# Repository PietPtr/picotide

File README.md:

# PicoTide

Repository filled with experimental crates and libraries for a [bittide](https://www.bittide.io/) style

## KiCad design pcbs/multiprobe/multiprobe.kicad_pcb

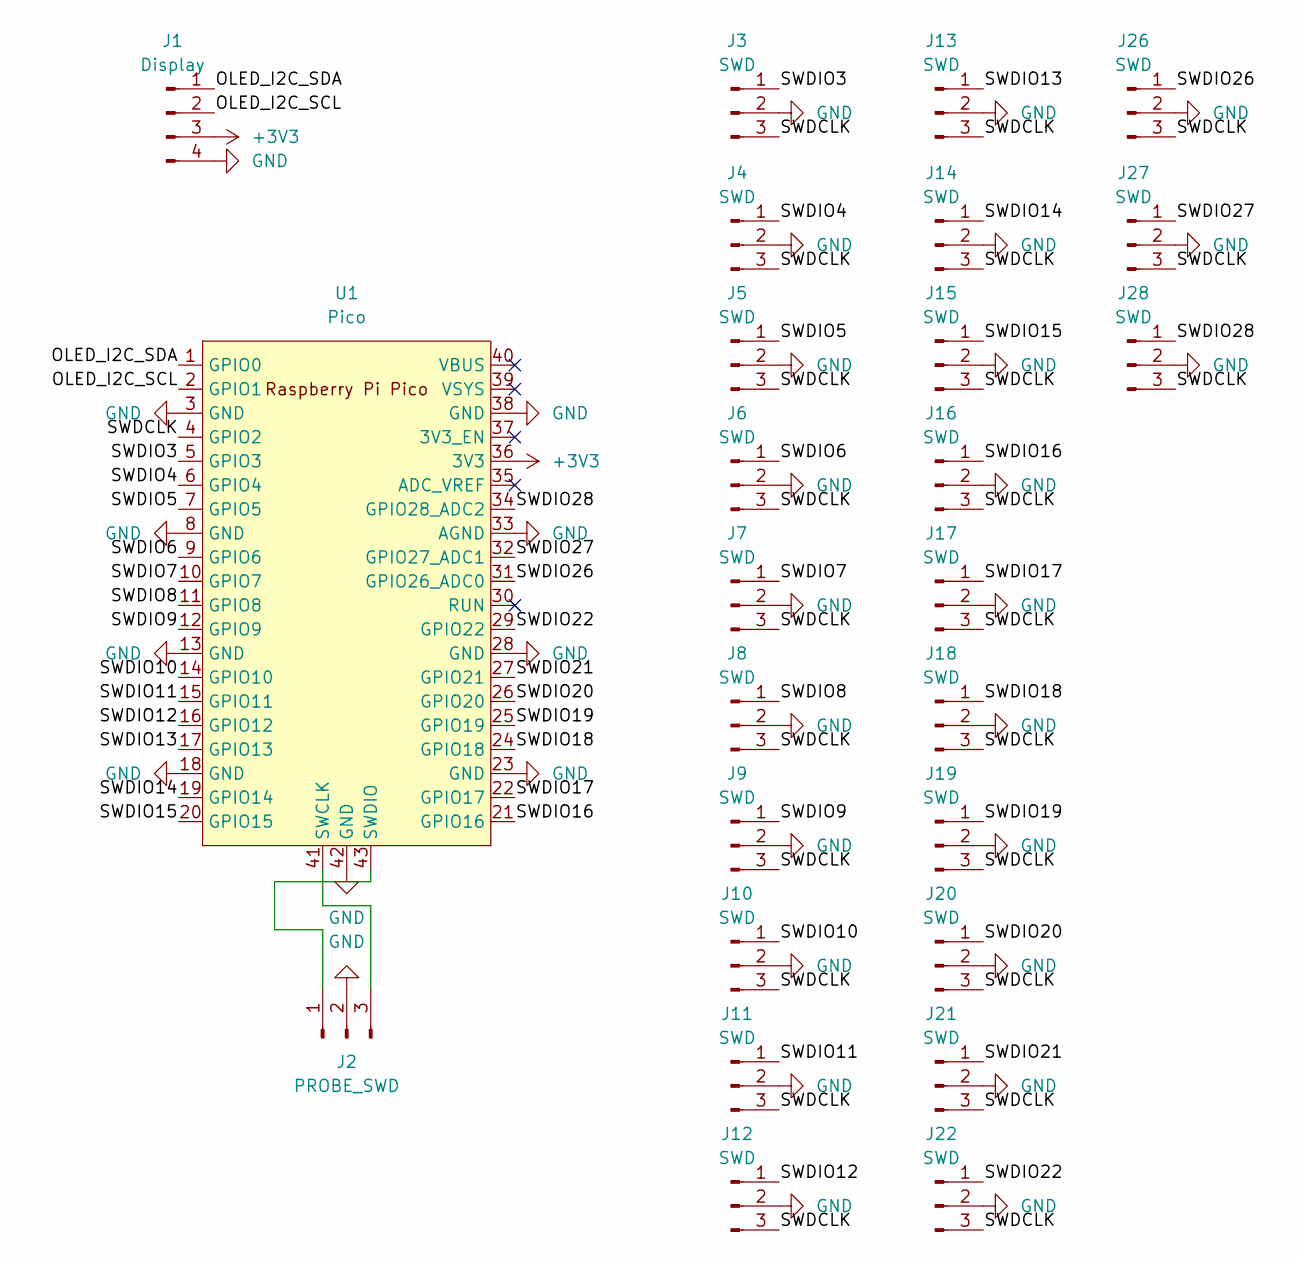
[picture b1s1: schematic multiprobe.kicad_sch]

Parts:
J1: Display; PinHeader_1x04_P2.54mm_Vertical
J2: PROBE_SWD; SWD
J3, J4, J5, J6, J7, J8, J9, J10, J11, J12, J13, J14, J15, J16, J17, J18, J19, J20, J21, J22, J26, J27, J28: SWD
U1: Pico; RPi_Pico_SMD_TH

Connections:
+3V3: J1.3, U1.36 (3V3)
/OLED_I2C_SCL: J1.2, U1.2 (GPIO1)
/OLED_I2C_SDA: J1.1, U1.1 (GPIO0)
/SWDCLK: J3.3, J4.3, J5.3, J6.3, J7.3, J8.3, J9.3, J10.3, J11.3, J12.3, J13.3, J14.3, J15.3, J16.3, J17.3, J18.3, J19.3, J20.3, J21.3, J22.3, J26.3, J27.3, J28.3, U1.4 (GPIO2)
/SWDIO3: J3.1, U1.5 (GPIO3)
/SWDIO4: J4.1, U1.6 (GPIO4)
/SWDIO5: J5.1, U1.7 (GPIO5)
/SWDIO6: J6.1, U1.9 (GPIO6)
/SWDIO7: J7.1, U1.10 (GPIO7)
/SWDIO8: J8.1, U1.11 (GPIO8)
/SWDIO9: J9.1, U1.12 (GPIO9)
/SWDIO10: J10.1, U1.14 (GPIO10)
/SWDIO11: J11.1, U1.15 (GPIO11)
/SWDIO12: J12.1, U1.16 (GPIO12)
/SWDIO13: J13.1, U1.17 (GPIO13)
/SWDIO14: J14.1, U1.19 (GPIO14)
/SWDIO15: J15.1, U1.20 (GPIO15)
/SWDIO16: J16.1, U1.21 (GPIO16)
/SWDIO17: J17.1, U1.22 (GPIO17)
/SWDIO18: J18.1, U1.24 (GPIO18)
/SWDIO19: J19.1, U1.25 (GPIO19)
/SWDIO20: J20.1, U1.26 (GPIO20)
/SWDIO21: J21.1, U1.27 (GPIO21)
/SWDIO22: J22.1, U1.29 (GPIO22)
/SWDIO26: J26.1, U1.31 (GPIO26_ADC0)
/SWDIO27: J27.1, U1.32 (GPIO27_ADC1)
/SWDIO28: J28.1, U1.34 (GPIO28_ADC2)
GND: J1.4, J2.2, J3.2, J4.2, J5.2, J6.2, J7.2, J8.2, J9.2, J10.2, J11.2, J12.2, J13.2, J14.2, J15.2, J16.2, J17.2, J18.2, J19.2, J20.2, J21.2, J22.2, J26.2, J27.2, J28.2, U1.3 (GND), U1.8 (GND), U1.13 (GND), U1.18 (GND), U1.23 (GND), U1.28 (GND), U1.33 (AGND), U1.38 (GND), U1.42 (GND)
unnamed: J2.1, U1.43 (SWDIO)
unnamed: J2.3, U1.41 (SWCLK)

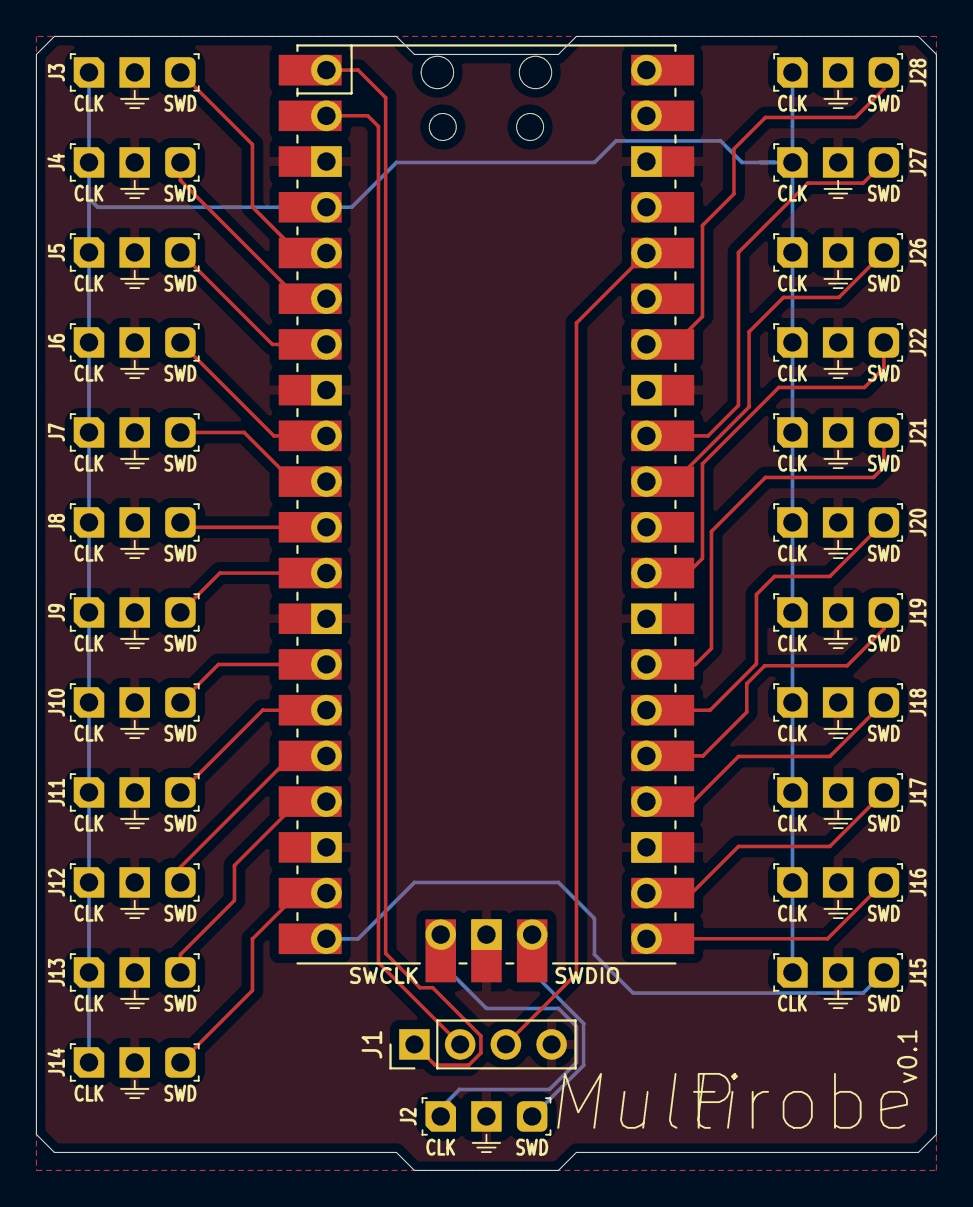
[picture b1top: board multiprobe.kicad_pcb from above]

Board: 2 copper layers, 50.0 x 63.0 mm, 26 parts (0 on the bottom side), 30 nets.

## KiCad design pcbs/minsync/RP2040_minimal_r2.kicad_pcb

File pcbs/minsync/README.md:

# `minsync`

A minimal testbed for a RP2040-based board with an Si5351 as a clock source instead of the usual 12MHz crystal. 

# IO:

- Four clusters of six GPIO pins and 5V + GND power pins to allow easy chaining of the board.
- Headers for SWD flashing
- A bootsel button
- Testpoint for a gpout pin for debugging internal clocks

# Components

Si5351A (0.77): https://jlcpcb.com/partdetail/skyworks_siliconLabs-SI5351A_BGTR/C504891 
25 MHz crystal (0.25): https://jlcpcb.com/partdetail/Ndk-NX3225GA_25_000M_STD_CRG2/C1985619
RP2040 (0.95): https://jlcpcb.com/partdetail/RaspberryPi-RP2040/C2040
Voltage regulator (0.51): https://jlcpcb.com/partdetail/Onsemi-NCP1117DT33G/C154606
quad SPI flash (0.51): https://jlcpcb.com/partdetail/WinbondElec-W25Q128JVSIQ/C97521
Button for reset (0.57): https://jlcpcb.com/partdetail/ck-KMR221GLFS/C72443
Male headers x4 (0.60): https://jlcpcb.com/partdetail/225573-A2005WV2x5P/C225290

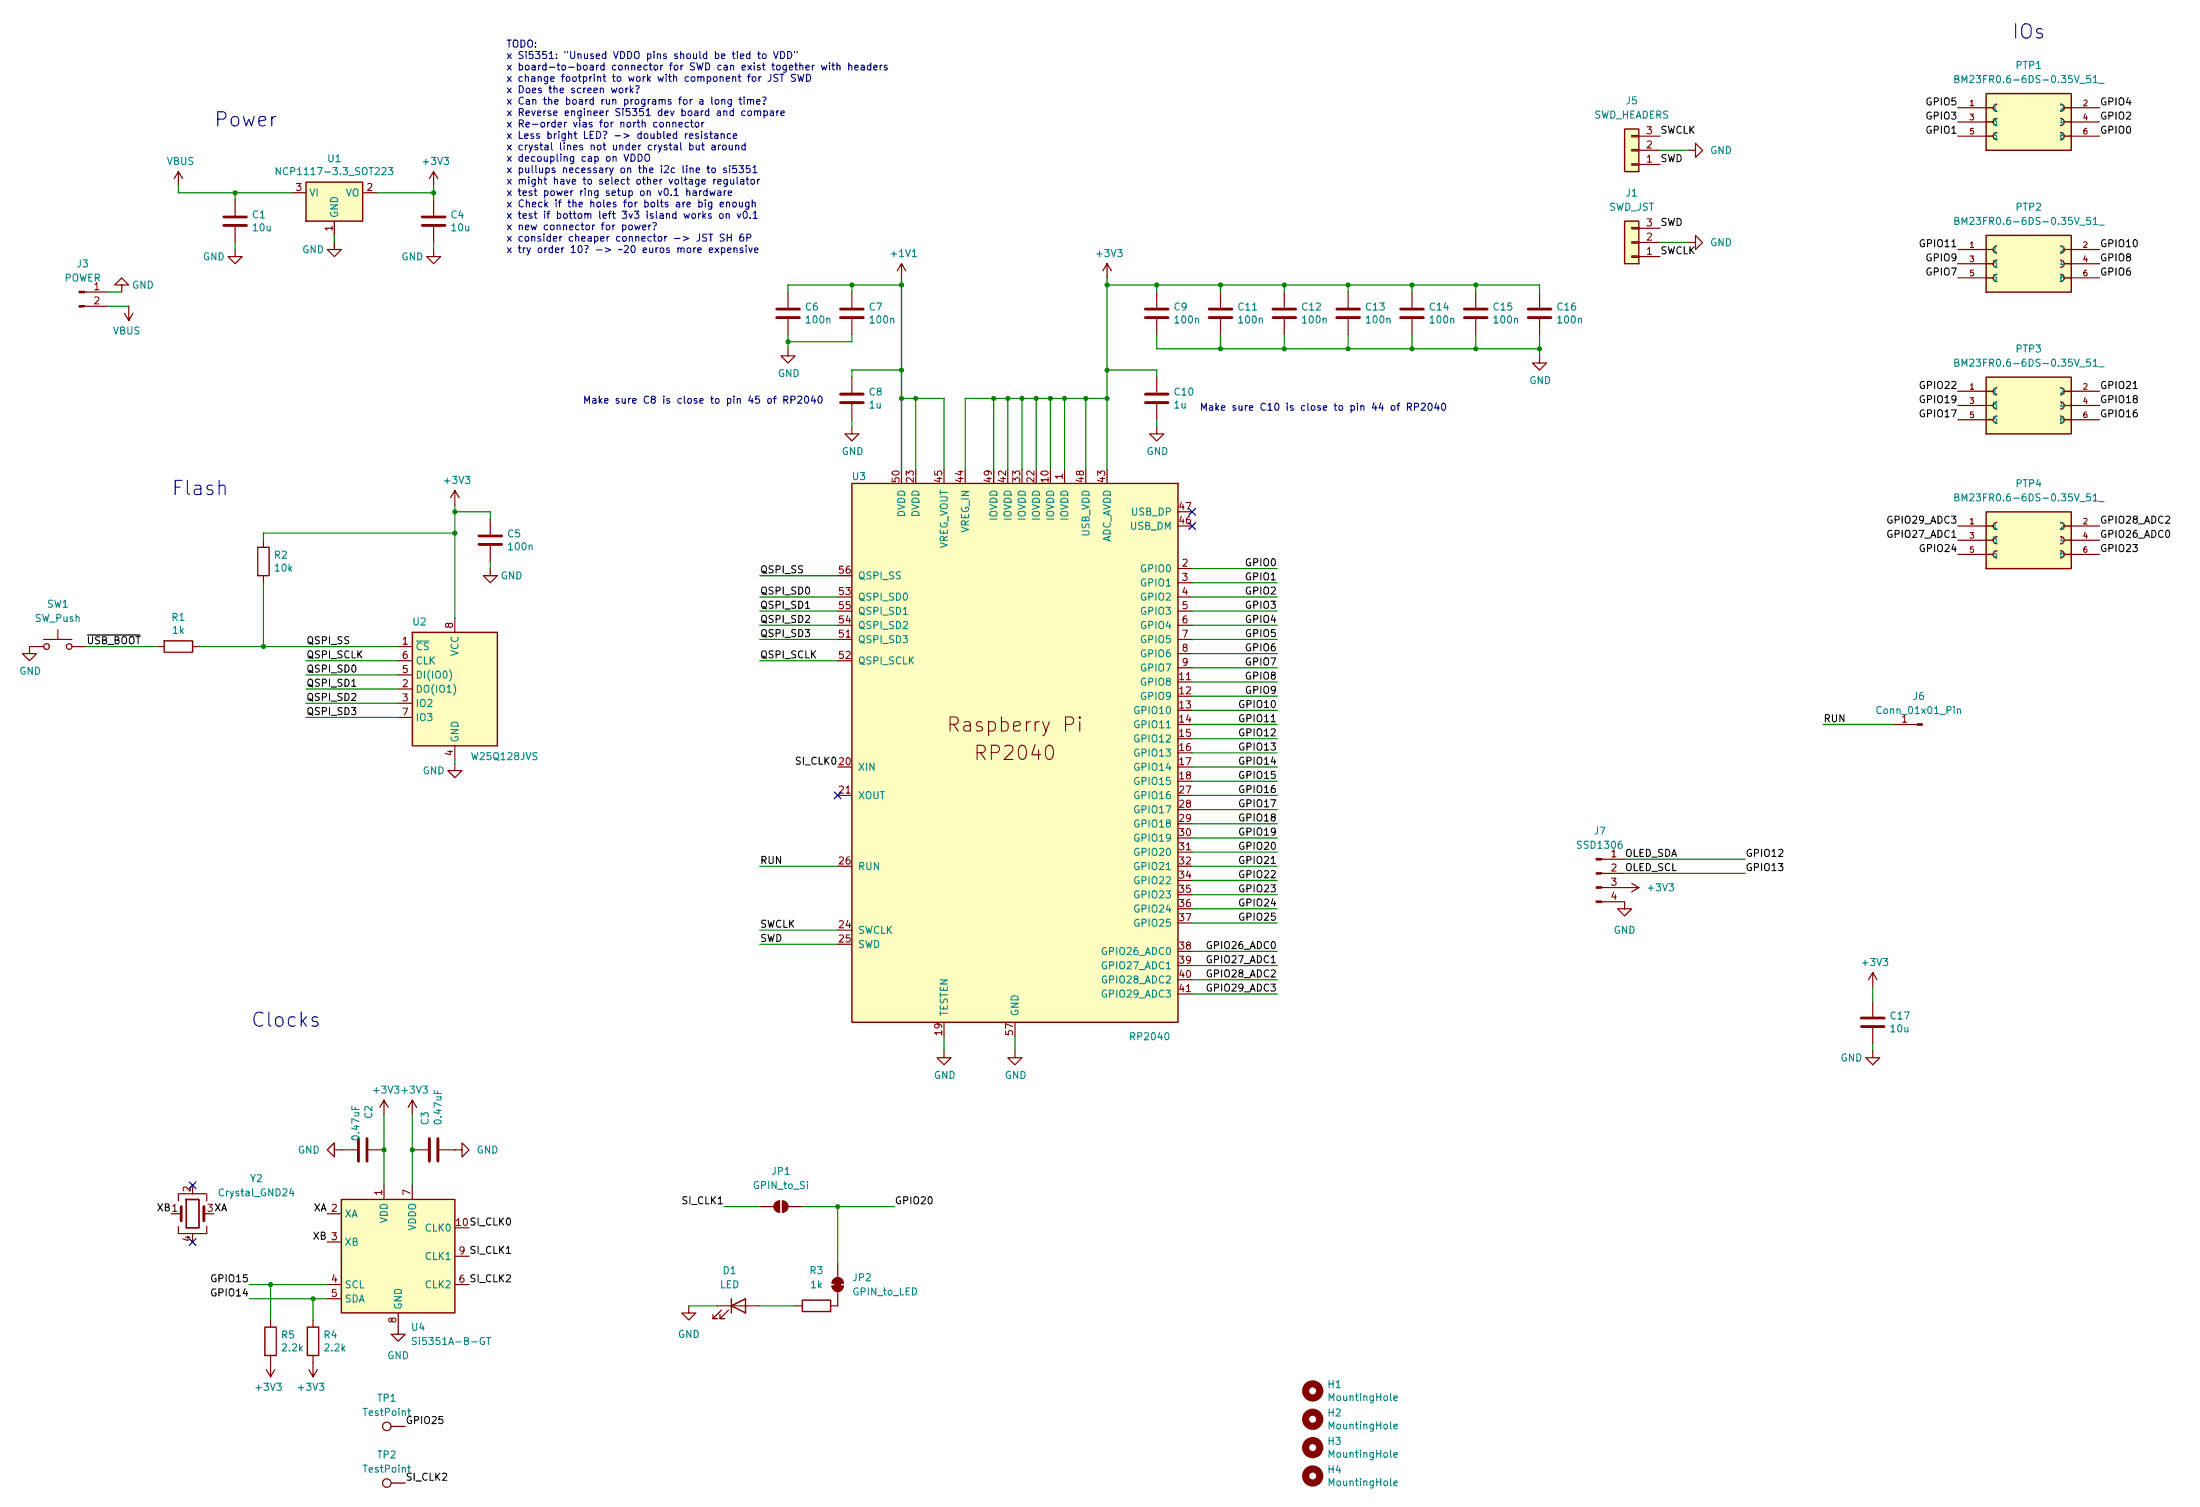
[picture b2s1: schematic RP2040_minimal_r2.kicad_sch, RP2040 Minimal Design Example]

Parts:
C1, C4, C17: 10u; C_0805_2012Metric
C2, C3: 0.47uF; C_0603_1608Metric
C5, C6, C7, C9, C11, C12, C13, C14, C15, C16: 100n; C_0402_1005Metric
C8, C10: 1u; C_0402_1005Metric
D1: LED; LED_0603_1608Metric
H1, H2, H3, H4: MountingHole; MountingHole_2.7mm_M2.5
J1: SWD_JST; JST_SH_BM03B-SRSS-TB_1x03-1MP_P1.00mm_Vertical; LCSC C160389
J3: POWER; PinHeader_1x02_P2.54mm_Vertical
J5: SWD_HEADERS; PinHeader_1x03_P2.54mm_Vertical
J6: Conn_01x01_Pin; PinHeader_1x01_P1.27mm_Vertical
J7: SSD1306; PinHeader_1x04_P2.54mm_Vertical
JP1: GPIN_to_Si; SolderJumper-2_P1.3mm_Open_RoundedPad1.0x1.5mm
JP2: GPIN_to_LED; SolderJumper-2_P1.3mm_Bridged_RoundedPad1.0x1.5mm
PTP1, PTP2, PTP3, PTP4: BM23FR0.6-6DS-0.35V_51_; JST_SH_BM06B-SRSS-TB_1x06-1MP_P1.00mm_Vertical; PARTREV 16.11.07; DigiKey_Part_Number 26-BM23FR0.6-6DS-0.35V(51)TR-ND
R1, R3: 1k; R_0402_1005Metric
R2: 10k; R_0402_1005Metric
R4, R5: 2.2k; R_0402_1005Metric
SW1: SW_Push; TS-1187A-PushButton; LCSC C72443
TP1, TP2: TestPoint; PinHeader_1x01_P2.54mm_Vertical
U1: NCP1117-3.3_SOT223; SOT-223-3_TabPin2; LCSC C154606
U2: W25Q128JVS; SOIC-8_5.23x5.23mm_P1.27mm; LCSC C97521
U3: RP2040; RP2040-QFN-56; LCSC C2040
U4: Si5351A-B-GT; MSOP-10_3x3mm_P0.5mm; LCSC C504891
Y2: Crystal_GND24; Crystal_SMD_3225-4Pin_3.2x2.5mm; LCSC C1985619

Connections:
+1V1: C6.1, C7.1, C8.1, U3.23 (DVDD), U3.45 (VREG_VOUT), U3.50 (DVDD)
+3V3: C2.1, C3.1, C4.1, C5.1, C9.1, C10.1, C11.1, C12.1, C13.1, C14.1, C15.1, C16.1, C17.1, J7.3, R2.1, R4.2, R5.2, U1.2 (VO), U2.8 (VCC), U3.1 (IOVDD), U3.10 (IOVDD), U3.22 (IOVDD), U3.33 (IOVDD), U3.42 (IOVDD), U3.43 (ADC_AVDD), U3.44 (VREG_IN), U3.48 (USB_VDD), U3.49 (IOVDD), U4.1 (VDD), U4.7 (VDDO)
/GPIO0: PTP1.6, U3.2 (GPIO0)
/GPIO1: PTP1.5, U3.3 (GPIO1)
/GPIO2: PTP1.4, U3.4 (GPIO2)
/GPIO3: PTP1.3, U3.5 (GPIO3)
/GPIO4: PTP1.2, U3.6 (GPIO4)
/GPIO5: PTP1.1, U3.7 (GPIO5)
/GPIO6: PTP2.6, U3.8 (GPIO6)
/GPIO7: PTP2.5, U3.9 (GPIO7)
/GPIO8: PTP2.4, U3.11 (GPIO8)
/GPIO9: PTP2.3, U3.12 (GPIO9)
/GPIO10: PTP2.2, U3.13 (GPIO10)
/GPIO11: PTP2.1, U3.14 (GPIO11)
/GPIO12: J7.1, U3.15 (GPIO12)
/GPIO13: J7.2, U3.16 (GPIO13)
/GPIO14: R4.1, U3.17 (GPIO14), U4.5 (SDA)
/GPIO15: R5.1, U3.18 (GPIO15), U4.4 (SCL)
/GPIO16: PTP3.6, U3.27 (GPIO16)
/GPIO17: PTP3.5, U3.28 (GPIO17)
/GPIO18: PTP3.4, U3.29 (GPIO18)
/GPIO19: PTP3.3, U3.30 (GPIO19)
/GPIO20: JP1.2 (B), JP2.2 (B), U3.31 (GPIO20)
/GPIO21: PTP3.2, U3.32 (GPIO21)
/GPIO22: PTP3.1, U3.34 (GPIO22)
/GPIO23: PTP4.6, U3.35 (GPIO23)
/GPIO24: PTP4.5, U3.36 (GPIO24)
/GPIO25: TP1.1, U3.37 (GPIO25)
/GPIO26_ADC0: PTP4.4, U3.38 (GPIO26_ADC0)
/GPIO27_ADC1: PTP4.3, U3.39 (GPIO27_ADC1)
/GPIO28_ADC2: PTP4.2, U3.40 (GPIO28_ADC2)
/GPIO29_ADC3: PTP4.1, U3.41 (GPIO29_ADC3)
/QSPI_SCLK: U2.6 (CLK), U3.52 (QSPI_SCLK)
/QSPI_SD0: U2.5 (DI(IO0)), U3.53 (QSPI_SD0)
/QSPI_SD1: U2.2 (DO(IO1)), U3.55 (QSPI_SD1)
/QSPI_SD2: U2.3 (IO2), U3.54 (QSPI_SD2)
/QSPI_SD3: U2.7 (IO3), U3.51 (QSPI_SD3)
/QSPI_SS: R1.1, R2.2, U2.1 (~CS), U3.56 (QSPI_SS)
/RUN: J6.1, U3.26 (RUN)
/SI_CLK0: U3.20 (XIN), U4.10 (CLK0)
/SI_CLK1: JP1.1 (A), U4.9 (CLK1)
/SI_CLK2: TP2.1, U4.6 (CLK2)
/SWCLK: J1.1, J5.3, U3.24 (SWCLK)
/SWD: J1.3, J5.1, U3.25 (SWD)
/XA: U4.2 (XA), Y2.3
/XB: U4.3 (XB), Y2.1
/~USB_BOOT: R1.2, SW1.2
GND: C1.2, C2.2, C3.2, C4.2, C5.2, C6.2, C7.2, C8.2, C9.2, C10.2, C11.2, C12.2, C13.2, C14.2, C15.2, C16.2, C17.2, D1.1 (K), J1.2, J3.1, J5.2, J7.4, SW1.1, U1.1 (GND), U2.4 (GND), U3.19 (TESTEN), U3.57 (GND), U4.8 (GND)
unnamed: D1.2 (A), R3.1
unnamed: JP2.1 (A), R3.2
VBUS: C1.1, J3.2, U1.3 (VI)

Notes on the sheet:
IOs
Power
Clocks
Make sure C8 is close to pin 45 of RP2040
Make sure C10 is close to pin 44 of RP2040
Flash
TODO: x Si5351: "Unused VDDO pins should be tied to VDD" x board-to-board connector for SWD can exist together with headers x change footprint to work with component for JST SWD x Does the screen work? x Can the board run programs for a long time? x Reverse engineer Si5351 dev board and compare x R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

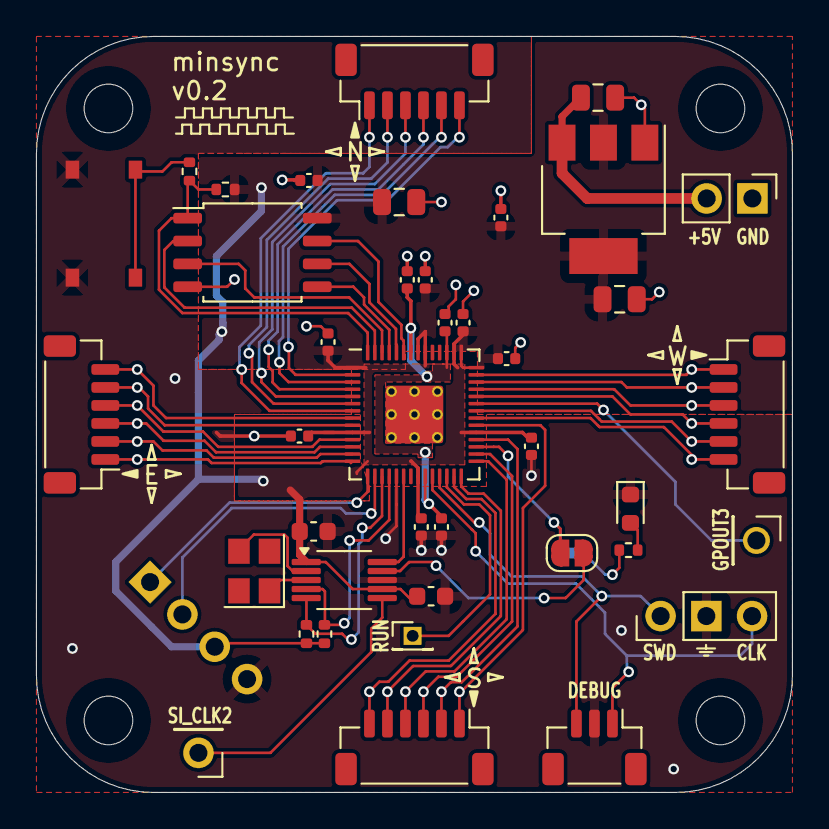
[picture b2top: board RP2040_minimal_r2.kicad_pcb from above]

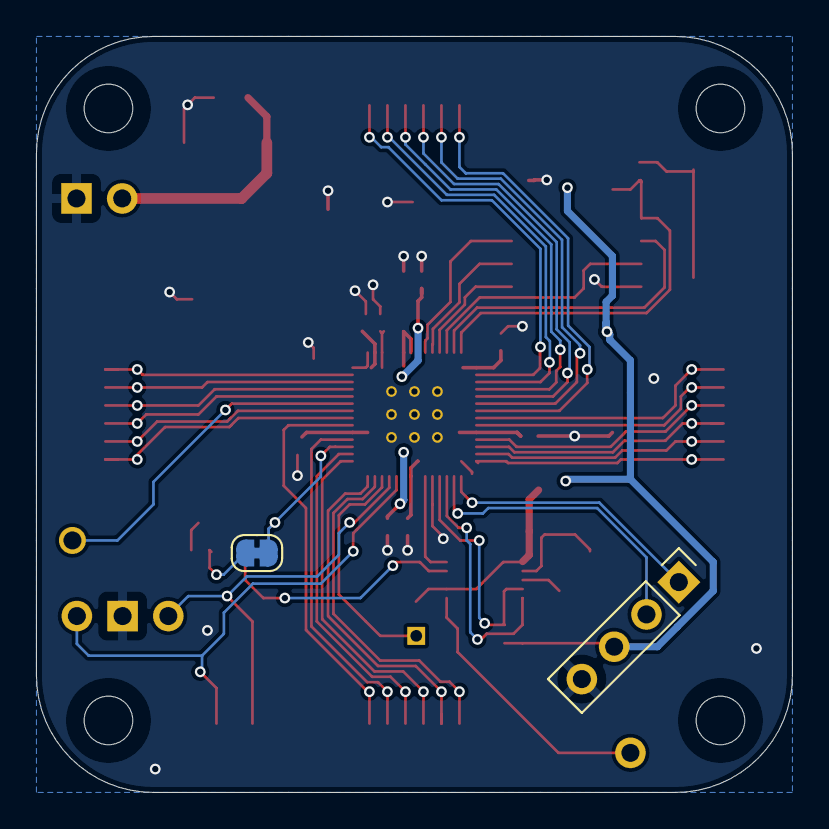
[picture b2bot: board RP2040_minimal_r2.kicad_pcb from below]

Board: 2 copper layers, 42.0 x 42.0 mm, 46 parts (2 on the bottom side), 51 nets.

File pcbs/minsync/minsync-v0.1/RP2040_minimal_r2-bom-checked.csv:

Comment,Designator,Footprint,LCSC
10u,"C1,C4,C17",Capacitor_SMD:C_0805_2012Metric,C15850
100n,"C2,C5,C6,C7,C9,C11,C12,C13,C14,C15,C16",Capacitor_SMD:C_0402_1005Metric,C1525
1u,"C8,C10",Capacitor_SMD:C_0402_1005Metric,C52923
LED,D1,LED_SMD:LED_0603_1608Metric,C2290
1k,R1,Resistor_SMD:R_0402_1005Metric,C11702
10k,R2,Resistor_SMD:R_0402_1005Metric,C25744
470R,R3,Resistor_SMD:R_0402_1005Metric,C25117
SW_Push,SW1,Button_Switch_SMD:SW_Push_SPST_NO_Alps_SKRK,C318884
NCP1117-3.3_SOT223,U1,Package_TO_SOT_SMD:SOT-223-3_TabPin2,C146799
W25Q128JVS,U2,Package_SO:SOIC-8_5.23x5.23mm_P1.27mm,C97521
RP2040,U3,RP2040_minimal:RP2040-QFN-56,C2040
Si5351A-B-GT,U4,Package_SO:MSOP-10_3x3mm_P0.5mm,C504891
Crystal_GND24,Y2,Crystal:Crystal_SMD_3225-4Pin_3.2x2.5mm,C1985619

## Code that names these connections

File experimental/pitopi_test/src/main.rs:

#![no_std]
#![no_main]

#[link_section = ".boot2"]
#[no_mangle]
#[used]
pub static BOOT2_FIRMWARE: [u8; 256] = rp2040_boot2::BOOT_LOADER_W25Q080;

use core::cell::RefCell;

use controllers::pid::PidSettings;
use controllers::si5351::Si5351Controller;
use cortex_m::asm;
use cortex_m_rt::exception;
use critical_section::Mutex;
#[allow(unused_imports)]
use defmt::{error, info, warn};
use defmt_rtt as _;
use fixed::types::I16F16;
use fugit::HertzU32;
use fugit::RateExtU32;
use panic_probe as _;
use pitopi::Pitopi;
use rp_pico::hal::gpin::GpIn0;
use rp_pico::hal::gpio::bank0::Gpio21;
use rp_pico::hal::gpio::FunctionClock;
use rp_pico::hal::gpio::Pin;
use rp_pico::hal::gpio::PullNone;
use rp_pico::hal::rosc::RingOscillator;
use rp_pico::hal::I2C;
use rp_pico::pac;
use rp_pico::{
    entry,
    hal::{
        clocks::{Clock, ClockSource, ClocksManager},
        gpio::{self, FunctionPio0, FunctionPio1},
        pio::PIOExt,
        pll::PLLConfig,
        sio::Sio,
    },
};

use bittide::bittide::BittideFifo;
use bittide_impls::chips::rp2040::Rp2040Links;
use si5351::Si5351;
use si5351::Si5351Device;

pub const EXTERNAL_XTAL_FREQ_HZ: HertzU32 = HertzU32::from_raw(12_000_000u32);

pub const SYS_PLL_CONFIG_100MHZ: PLLConfig = PLLConfig {
    vco_freq: HertzU32::MHz(1200),
    refdiv: 1,
    post_div1: 6,
    post_div2: 3,
};

/// The divisor of how many CPU cycles should pass before a new word is sent to all neigboring nodes.
pub const CLOCKS_PER_SYNC_WORD: u32 = 4096;

#[entry]
fn main() -> ! {
    let mut pac = pac::Peripherals::take().unwrap();
    let mut core = pac::CorePeripherals::take().unwrap();
    let sio = Sio::new(pac.SIO);

    let mut clocks = ClocksManager::new(pac.CLOCKS);

    let pins = gpio::Pins::new(
        pac.IO_BANK0,
        pac.PADS_BANK0,
        sio.gpio_bank0,
        &mut pac.RESETS,
    );

    // Run of Ring oscillatior (should be the default, unless other software has made changes to clocking, so set on startup)
    let rosc = RingOscillator::new(pac.ROSC);
    let rosc = rosc.initialize();

    clocks
        .system_clock
        .configure_clock(&rosc, rosc.get_freq())
        .unwrap();

    info!("Set clock to rosc {:?}MHz", rosc.get_freq().to_MHz());

    info!("Configuring Si5351");

    pins.gpio25
        .into_push_pull_output_in_state(gpio::PinState::High);

    let i2c = I2C::i2c1(
        pac.I2C1,
        pins.gpio26.reconfigure(),
        pins.gpio27.reconfigure(),
        100.kHz(),
        &mut pac.RESETS,
        &clocks.system_clock,
    );

    let mut si_clock = Si5351Device::new(i2c, false, 25_000_000);
    si_clock
        .init(si5351::CrystalLoad::_10)
        .expect("Cannot init clock.");

    si_clock
        .set_frequency(si5351::PLL::A, si5351::ClockOutput::Clk0, 13_000_000)
        .expect("Cannot set frequency");

    {
        let _gpout0_pin: Pin<Gpio21, FunctionClock, PullNone> = pins.gpio21.reconfigure();

        if let Err(e) = clocks
            .gpio_output0_clock
            .configure_clock(&clocks.system_clock, clocks.system_clock.get_freq())
        {
            warn!("Unable to route system clock to GPIO 21: {:?}", e);
        }
    };

    // Set up clock to run from gpio input from Si5351 clock
    let gpin0_pin = pins.gpio20.reconfigure();
    let gpin0: GpIn0 = GpIn0::new(gpin0_pin, EXTERNAL_XTAL_FREQ_HZ);

    clocks
        .system_clock
        .configure_clock(&gpin0, gpin0.get_freq())
        .unwrap();

    let (rx_pio, rx_sm0, rx_sm1, rx_sm2, rx_sm3) = pac.PIO0.split(&mut pac.RESETS);
    let (tx_pio, tx_sm0, tx_sm1, tx_sm2, tx_sm3) = pac.PIO1.split(&mut pac.RESETS);

    let rx0_data = pins.gpio3.into_function::<FunctionPio0>().into_dyn_pin();
    let rx0_clk = pins.gpio4.into_function::<FunctionPio0>().into_dyn_pin();
    let rx0_word = pins.gpio5.into_function::<FunctionPio0>().into_dyn_pin();

    let rx1_data = pins.gpio9.into_function::<FunctionPio0>().into_dyn_pin();
    let rx1_clk = pins.gpio10.into_function::<FunctionPio0>().into_dyn_pin();
    let rx1_word = pins.gpio11.into_function::<FunctionPio0>().into_dyn_pin();

    let rx2_data = pins.gpio15.into_function::<FunctionPio0>().into_dyn_pin();
    let rx2_clk = pins.gpio16.into_function::<FunctionPio0>().into_dyn_pin();
    let rx2_word = pins.gpio17.into_function::<FunctionPio0>().into_dyn_pin();

    let rx3_data = pins.gpio23.into_function::<FunctionPio0>().into_dyn_pin();
    let rx3_clk = pins.gpio24.into_function::<FunctionPio0>().into_dyn_pin();
    let rx3_word = pins.gpio28.into_function::<FunctionPio0>().into_dyn_pin();

    let tx0_data = pins.gpio0.into_function::<FunctionPio1>().into_dyn_pin();
    let tx0_clk = pins.gpio1.into_function::<FunctionPio1>().into_dyn_pin();
    let tx0_word = pins.gpio2.into_function::<FunctionPio1>().into_dyn_pin();

    let tx1_data = pins.gpio6.into_function::<FunctionPio1>().into_dyn_pin();
    let tx1_clk = pins.gpio7.into_function::<FunctionPio1>().into_dyn_pin();
    let tx1_word = pins.gpio8.into_function::<FunctionPio1>().into_dyn_pin();

    let tx2_data = pins.gpio12.into_function::<FunctionPio1>().into_dyn_pin();
    let tx2_clk = pins.gpio13.into_function::<FunctionPio1>().into_dyn_pin();
    let tx2_word = pins.gpio14.into_function::<FunctionPio1>().into_dyn_pin();

    let tx3_data = pins.gpio18.into_function::<FunctionPio1>().into_dyn_pin();
    let tx3_clk = pins.gpio19.into_function::<FunctionPio1>().into_dyn_pin();
    let tx3_word = pins.gpio22.into_function::<FunctionPio1>().into_dyn_pin();

    let mut pitopi = Pitopi::new(rx_pio, tx_pio);

    pitopi.install_programs();

    let (_, rx0, _, tx0) = pitopi
        .setup_link(
            pitopi::DEFAULT_LINK_CONFIG,
            rx_sm0,
            rx0_data,
            rx0_clk,
            rx0_word,
            tx_sm0,
            tx0_data,
            tx0_clk,
            tx0_word,
        )
        .unwrap();

    let (_, rx1, _, tx1) = pitopi
        .setup_link(
            pitopi::DEFAULT_LINK_CONFIG,
            rx_sm1,
            rx1_data,
            rx1_clk,
            rx1_word,
            tx_sm1,
            tx1_data,
            tx1_clk,
            tx1_word,
        )
        .unwrap();

    let (_, rx2, _, tx2) = pitopi
        .setup_link(
            pitopi::DEFAULT_LINK_CONFIG,
            rx_sm2,
            rx2_data,
            rx2_clk,
            rx2_word,
            tx_sm2,
            tx2_data,
            tx2_clk,
            tx2_word,
        )
        .unwrap();

    let (_, rx3, _, tx3) = pitopi
        .setup_link(
            pitopi::DEFAULT_LINK_CONFIG,
            rx_sm3,
            rx3_data,
            rx3_clk,
            rx3_word,
            tx_sm3,
            tx3_data,
            tx3_clk,
            tx3_word,
        )
        .unwrap();

    let sio_fifo = sio.fifo;

    let tide_fifos = [
        BittideFifo::new(),
        BittideFifo::new(),
        BittideFifo::new(),
        BittideFifo::new(),
    ];

    let tide_controller = bittide_impls::boards::pico1_and_si5351::Control::new(
        Si5351Controller::new(
            si_clock,
            4,
            PidSettings {
                kp: I16F16::from_num(0.01),
                ki: I16F16::from_num(0.00000001),
                kd: I16F16::from_num(0.01),
            },
        ),
        Rp2040Links::new(rx0, rx1, rx2, rx3, tx0, tx1, tx2, tx3),
        [true, true, true, true],
        bittide_impls::chips::rp2040::SioFifo(sio_fifo),
        tide_fifos,
    );

    critical_section::with(|cs| {
        GLOBAL_CONTROL.borrow(cs).replace(Some(tide_controller));
    });

    info!("Start.");
    bittide_impls::chips::rp2040::setup_interrupt(CLOCKS_PER_SYNC_WORD, &mut core.SYST);

    #[allow(clippy::empty_loop)]
    loop {
        for _ in 0..150000 {
            asm::nop();
        }
    }
}

static GLOBAL_CONTROL: Mutex<RefCell<Option<bittide_impls::boards::pico1_and_si5351::Control>>> =
    Mutex::new(RefCell::new(None));

#[exception]
fn SysTick() {
    static mut CONTROL: Option<bittide_impls::boards::pico1_and_si5351::Control> = None;

    if CONTROL.is_none() {
        critical_section::with(|cs| {
            let _ = CONTROL.insert(GLOBAL_CONTROL.borrow(cs).take().unwrap());
        });
    }

    if let Some(control) = CONTROL {
        control.interrupt().ok();
    }
}

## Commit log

2024-12-07 Add infra to check pico's own system clock
2024-12-07 Add test to dynamically adjust clock at runtime
2024-12-07 Add MHz conversion to measurement
2024-12-07 Add basic pio tests
2024-12-08 Add controllers
2024-12-08 Clean up clock tests crate
2024-12-08 Add pitopi communication tests
2024-12-09 Working pitopi demonstrator
2024-12-09 Reorganise
2024-12-09 Working demonstrator of pitopi with word
2024-12-09 Demonstrated between two picos
2024-12-11 Add infra for running bittide control
2024-12-11 Move tide functions to library
2024-12-13 Add debug stuff, and PID controller
2024-12-14 Tests on real hardware
2024-12-17 Add active RX link detection
2024-12-17 Working fbdiv based clock sync
2024-12-18 Add expose clock feature
2024-12-18 Si5351 clock generator tests
2024-12-18 Run pico off external clock signal
2024-12-19 Add WIP minsync PCB
2024-12-21 Route most of the minsync PCB
2024-12-27 Add Si5351 controller
2025-01-10 Use new GpIn from rp hal
2025-01-10 Move code to libraries
2025-01-10 Test pitopi lib
2025-01-10 Move systick
2025-01-11 Add bitsurf
2025-01-11 Update minsync PCB
2025-01-11 Add BOM and CPL of minsync v0.1
2025-01-11 Clock experiments
2025-01-12 Add flash all routine
2025-01-13 Switch to 2x4P headers
2025-01-14 Use 2x4P headers for connectors
2025-01-14 Cleanups
2025-01-15 Flashing improvements
2025-01-17 Add library to easily build the same binary with different constants
2025-01-18 Add more flashing utilities
2025-01-19 Implement minsync_connect v0.1
2025-01-19 Dry run ordering minsync and minsync connect v0.1
2025-01-19 Update TODO
2025-01-20 Clean up build and flash
2025-01-22 Add minsync BSP + example
2025-01-22 Get minsync PCB ready for order
2025-01-23 Plot fp text
2025-01-24 Pos changes
2025-01-25 Order minsync
2025-02-04 Add surf lang ideas draft
2025-02-05 Debug minsync PCB
2025-02-06 Add todo's
2025-02-06 Test more of the hardware / make PCB modifications for v0.2
2025-02-09 minsync: Implement fixes for problems in v0.1, bump version to v0.2.
2025-02-09 Add surf proc macro parsing
2025-02-09 Implement surf proc and rewrite state machines in monte carlo example
2025-02-10 Update minsync bsp for v0.2
    Drop support for v0.1, doesn't work anyway :)
2025-02-11 Work on node / program types for surf-lang
2025-02-13 Update PCB BOM and TOdo's
2025-02-13 FIR example WIP
2025-02-16 Fit FIR to node
2025-02-16 Add pullups for si5351, change SWD plug footprint
2025-02-16 Try new pitopi connector
2025-02-16 Use JST SH headers for pitopi
2025-02-20 Add vias before JST connectors
2025-03-07 Productionize minsync v0.2
2025-03-07 Research I2C blocking issues for Si configuration
2025-03-09 Fix button, reroute some tracks
2025-03-19 Order minsync v0.2
2025-04-18 minsync v0.2 bringup
2025-04-18 Add double minsync installation
2025-04-19 Move common clocking code to the BSP
2025-04-19 Move common graphics code to BSP
2025-04-20 Debug pitopi interface for minsync v0.2
2025-04-20 Work out link configurations for minsync
2025-04-20 Move minsync setup to impls crate
2025-04-20 Setup Bittide on double minsync
2025-04-20 Add debugging crate
2025-04-21 Add multiprobe breakout PCB
2025-04-22 Order multiprobe v0.1
2025-04-24 Refactor to make testing frequency controllers possible
